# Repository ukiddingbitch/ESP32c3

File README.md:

# ESP32-C3

MIFA-F4 is a development board based on the **Espressif ESP32-C3FH4**, with 4 MB of flash, 2.4 GHz Wi-Fi, and Bluetooth LE. A meandered inverted-F antenna (MIFA) is etched into the PCB. Contacts on both sides of the board edge form the USB-C interface.

## Hardware

| Feature | Specification |
| --- | --- |
| Board size | 24.54 × 29.90 mm |
| PCB | 0.8 mm, two-layer FR-4 with an ENIG finish and castellated edge holes |
| Antenna | Meandered PCB antenna based on TI AN043 |
| Headers | Two rows of eight pins on a 2.54 mm pitch, spaced 20.32 mm apart center to center |
| Buttons | BOOT pulls GPIO9 low. RESET pulls EN low. |
| Assembly | 35 components per board |
| Panel | Six boards in a 3 × 2 layout, 95.62 × 80 mm, 210 component placements |

## Board

**Six-board assembly panel**

endfa

## Opening the design in KiCad

Download or clone the full repository to include the project libraries and 3D models. Open the [MIFA-F4 project](esp32c3mini-MIFA-F4/esp32c3mini.kicad_pro) in **KiCad 10**. Select the `.kicad_sch` file to view the schematic or the `.kicad_pcb` file to inspect the board layout. In the PCB Editor, press **Alt+3** to open the 3D Viewer.

## Fabrication and assembly

Choose the files for either a single board or a six-board panel. Use all three files from the same row.

| Format | PCB fabrication | Assembly parts list | Component positions and rotations |
| --- | --- | --- | --- |
| Single board | [Gerber ZIP](esp32c3mini-MIFA-F4/esp32c3mini-Gerber.zip) | [BOM](esp32c3mini-MIFA-F4/esp32c3mini-BOM.csv) | [CPL](esp32c3mini-MIFA-F4/esp32c3mini-CPL.csv) |
| Six-board panel | [Panel Gerber ZIP](esp32c3mini-MIFA-F4/panel/esp32c3mini-panel-Gerber.zip) | [Panel BOM](esp32c3mini-MIFA-F4/panel/esp32c3mini-panel-BOM.csv) | [Panel CPL](esp32c3mini-MIFA-F4/panel/esp32c3mini-panel-CPL.csv) |

For JLCPCB, upload the Gerber ZIP when ordering the PCB, then upload the matching BOM and CPL during assembly setup. Five assembled panels yield 30 individual boards.

## Prototype status and known limitations

**This board has not been physically tested.** The MIFA-F4 layout passed KiCad connectivity and schematic parity checks. Boot reliability, USB-C operation, power stability, and RF performance still require measurements on assembled hardware. Build and test a small prototype batch before ordering a production run.

### Before assembly

- Confirm the **0.8 mm PCB thickness** with the manufacturer. The board edge forms the USB-C mating surface, so thickness and routing tolerances affect the fit.
- Check the regulator orientation in the assembly preview. With the component side facing up and USB-C at the top, **U2 should have three leads toward USB-C and pin 1 at the upper right**. On the panel, the corresponding references are U102 through U602.

### First-prototype checks

| Area | What to verify |
| --- | --- |
| Power and boot | Check for a short between 3.3 V and GND before applying power. Use a current-limited supply for the first power-up, measure the 3.3 V rail, and check for voltage dips or resets during Wi-Fi transmission. Repeat cold starts to check boot reliability. |
| USB-C | Test plug fit, power delivery, USB detection, and firmware flashing in both plug orientations. Check that the connection stays stable during normal cable movement. Contact durability over repeated insertions is unverified. |
| BOOT and RESET | Confirm that holding BOOT while pressing and releasing RESET enters download mode, and that pressing RESET alone restarts the application. |
| Wi-Fi and antenna | Test a board **after separating it from the panel**. Compare signal strength and packet loss against a known-good ESP32-C3 board at the same distance and orientation on low, middle, and high Wi-Fi channels. Measure antenna return loss (S11) with a calibrated vector network analyzer to check impedance matching. |
| Board headers | Verify the 5 V, 3.3 V, and ground pins before connecting peripherals. Check the exposed GPIOs against the schematic and confirm the mechanical fit in the intended breadboard or carrier. |

The antenna layout follows TI AN043. Its range and susceptibility to interference from the nearby 40 MHz crystal are unverified on this PCB. See the [F4 validation notes](esp32c3mini-MIFA-F4/00-HOLD.txt) for layout dimensions and additional test details.

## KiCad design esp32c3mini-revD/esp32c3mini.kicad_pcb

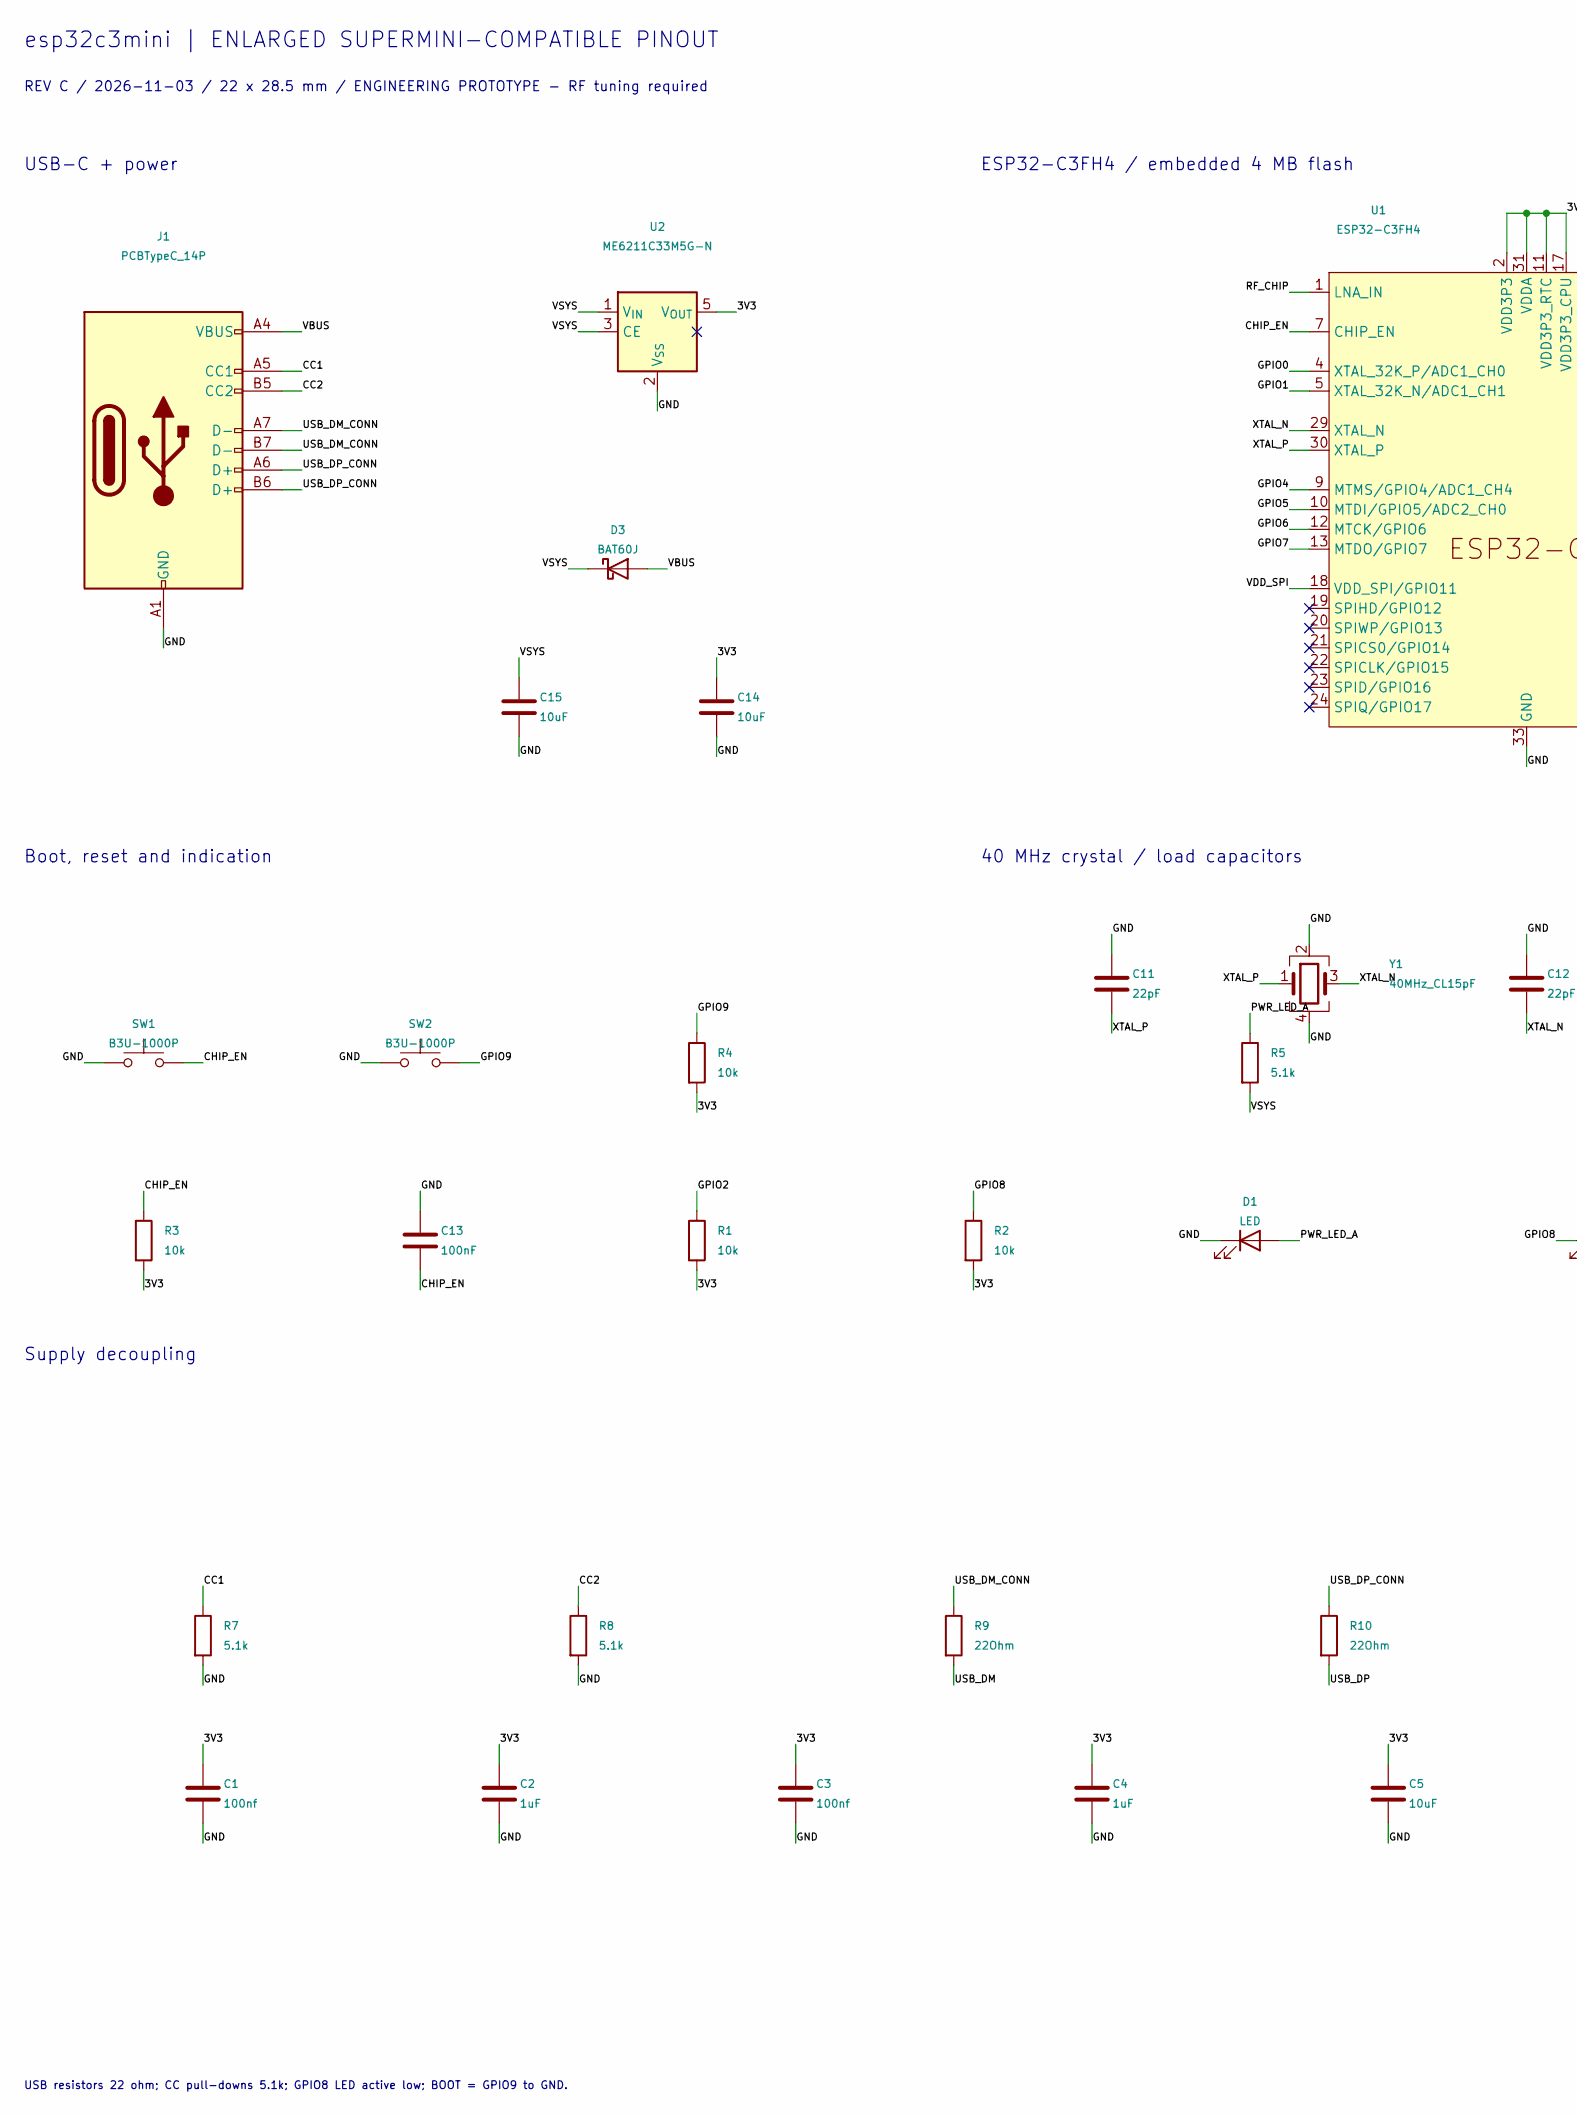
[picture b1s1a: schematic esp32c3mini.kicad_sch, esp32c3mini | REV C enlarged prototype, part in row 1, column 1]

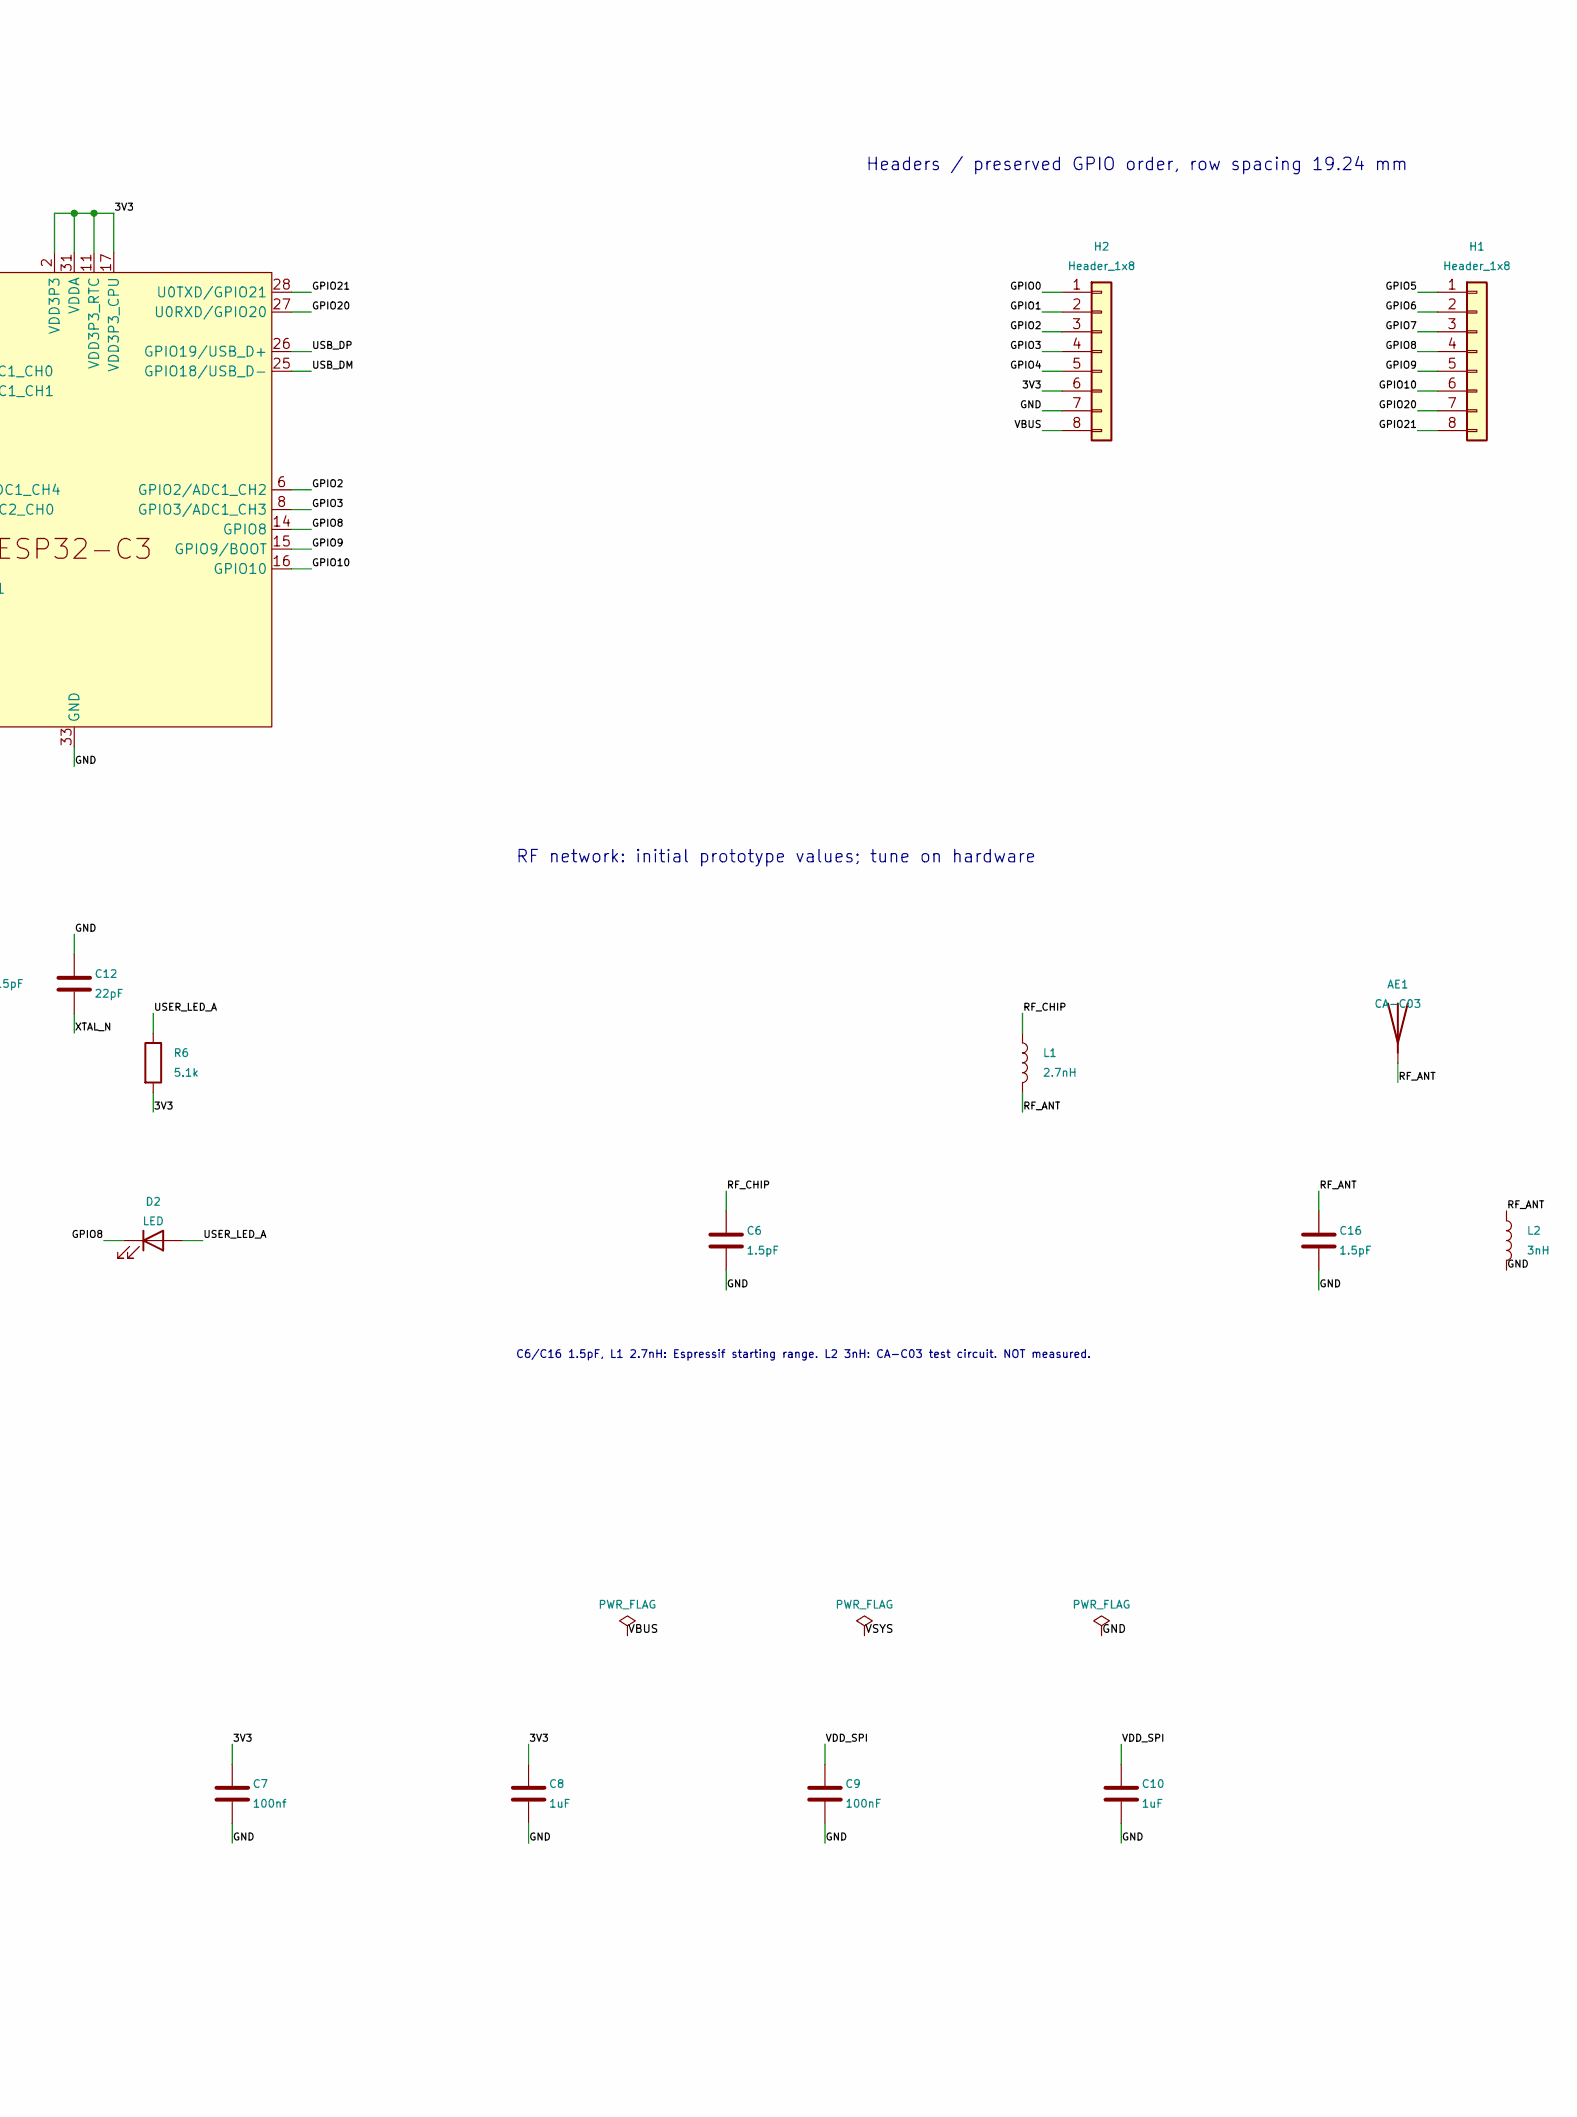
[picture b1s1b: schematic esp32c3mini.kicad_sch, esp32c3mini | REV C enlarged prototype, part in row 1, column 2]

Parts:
AE1: CA-C03; Antenna_CA_C03; MPN CA-C03; LCSC C9900104680
C1, C3, C7: 100nf; C_0201_0603Metric; MPN GRM033R61A104KE15D; LCSC C76934
C2, C4, C8, C10: 1uF; C_0201_0603Metric; MPN CL03A105KQ3CSNC; LCSC C318541
C5, C14, C15: 10uF; C_0402_1005Metric; MPN CL05A106MP5NUNC; LCSC C315248
C6, C16: 1.5pF; C_0201_0603Metric; MPN GRM0335C1H1R5BA01D; LCSC C161414
C9, C13: 100nF; C_0201_0603Metric; MPN GRM033R61A104KE15D; LCSC C76934
C11, C12: 22pF; C_0201_0603Metric; MPN GJM0335C1E220JB01D; LCSC C237453
D1: LED; LED_0603_1608Metric; MPN KT-0603R; LCSC C2286
D2: LED; LED_0603_1608Metric; MPN KT-0603B; LCSC C2288
D3: BAT60J; D_SOD-323; MPN BAT60JFILM; LCSC C133103
H1: Header_1x8; Header_Right
H2: Header_1x8; Header_Left
J1: PCBTypeC_14P; MPN PCB_EDGE_CONTACTS
L1: 2.7nH; L_0201_0603Metric; MPN LQP03TN2N7C02D; LCSC C185546
L2: 3nH; L_0201_0603Metric; MPN LQP03TN3N0C02D; LCSC C162614
R1, R2, R3, R4: 10k; R_0201_0603Metric; MPN 0201WMF1002TEE; LCSC C473048
R5, R6, R7, R8: 5.1k; R_0201_0603Metric; MPN 0201WMF5101TEE; LCSC C270344
R9, R10: 22Ohm; R_0201_0603Metric; MPN 0201WMF220JTEE; LCSC C270355
SW1, SW2: B3U-1000P; SW_SPST_B3U-1000P; MPN B3U-1000P; LCSC C231329
U1: ESP32-C3FH4; QFN-32-1EP_5x5mm_P0.5mm_EP3.45x3.45mm; MPN ESP32-C3FH4; LCSC C2858491
U2: ME6211C33M5G-N; SOT-23-5; MPN ME6211C33M5G-N; LCSC C82942
Y1: 40MHz_CL15pF; Crystal_SMD_3225-4Pin_3.2x2.5mm; MPN X322540MPB4SI; LCSC C9010

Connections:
/3V3: C1.1, C2.1, C3.1, C4.1, C5.1, C7.1, C8.1, C14.1, H2.6, R1.2, R2.2, R3.2, R4.2, R6.2, U1.2 (VDD3P3), U1.3 (VDD3P3), U1.11 (VDD3P3_RTC), U1.17 (VDD3P3_CPU), U1.31 (VDDA), U1.32 (VDDA), U2.5 (V_{OUT})
/CC1: J1.A5 (CC1), R7.1
/CC2: J1.B5 (CC2), R8.1
/CHIP_EN: C13.2, R3.1, SW1.2, U1.7 (CHIP_EN)
/GND: C1.2, C2.2, C3.2, C4.2, C5.2, C6.2, C7.2, C8.2, C9.2, C10.2, C11.1, C12.1, C13.1, C14.2, C15.2, C16.2, D1.1 (K), H2.7, J1.A1 (GND), J1.A12 (GND), J1.B1 (GND), J1.B12 (GND), L2.2, R7.2, R8.2, SW1.1, SW2.1, U1.33 (GND), U2.2 (V_{SS}), Y1.2, Y1.4
/GPIO0: H2.1, U1.4 (XTAL_32K_P/ADC1_CH0)
/GPIO1: H2.2, U1.5 (XTAL_32K_N/ADC1_CH1)
/GPIO2: H2.3, R1.1, U1.6 (GPIO2/ADC1_CH2)
/GPIO3: H2.4, U1.8 (GPIO3/ADC1_CH3)
/GPIO4: H2.5, U1.9 (MTMS/GPIO4/ADC1_CH4)
/GPIO5: H1.1, U1.10 (MTDI/GPIO5/ADC2_CH0)
/GPIO6: H1.2, U1.12 (MTCK/GPIO6)
/GPIO7: H1.3, U1.13 (MTDO/GPIO7)
/GPIO8: D2.1 (K), H1.4, R2.1, U1.14 (GPIO8)
/GPIO9: H1.5, R4.1, SW2.2, U1.15 (GPIO9/BOOT)
/GPIO10: H1.6, U1.16 (GPIO10)
/GPIO20: H1.7, U1.27 (U0RXD/GPIO20)
/GPIO21: H1.8, U1.28 (U0TXD/GPIO21)
/PWR_LED_A: D1.2 (A), R5.1
/RF_ANT: AE1.1, C16.1, L1.2, L2.1
/RF_CHIP: C6.1, L1.1, U1.1 (LNA_IN)
/USB_DM: R9.2, U1.25 (GPIO18/USB_D-)
/USB_DM_CONN: J1.A7 (D-), J1.B7 (D-), R9.1
/USB_DP: R10.2, U1.26 (GPIO19/USB_D+)
/USB_DP_CONN: J1.A6 (D+), J1.B6 (D+), R10.1
/USER_LED_A: D2.2 (A), R6.1
/VBUS: D3.2 (A), H2.8, J1.A4 (VBUS), J1.A9 (VBUS), J1.B4 (VBUS), J1.B9 (VBUS)
/VDD_SPI: C9.1, C10.1, U1.18 (VDD_SPI/GPIO11)
/VSYS: C15.1, D3.1 (K), R5.2, U2.1 (V_{IN}), U2.3 (CE)
/XTAL_N: C12.2, U1.29 (XTAL_N), Y1.3
/XTAL_P: C11.2, U1.30 (XTAL_P), Y1.1

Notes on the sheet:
esp32c3mini | ENLARGED SUPERMINI-COMPATIBLE PINOUT
REV C / 2026-11-03 / 22 x 28.5 mm / ENGINEERING PROTOTYPE - RF tuning required
USB-C + power
ESP32-C3FH4 / embedded 4 MB flash
Headers / preserved GPIO order, row spacing 19.24 mm
Boot, reset and indication
40 MHz crystal / load capacitors
RF network: initial prototype values; tune on hardware
Supply decoupling
C6/C16 1.5pF, L1 2.7nH: Espressif starting range. L2 3nH: CA-C03 test circuit. NOT measured.
USB resistors 22 ohm; CC pull-downs 5.1k; GPIO8 LED active low; BOOT = GPIO9 to GND.

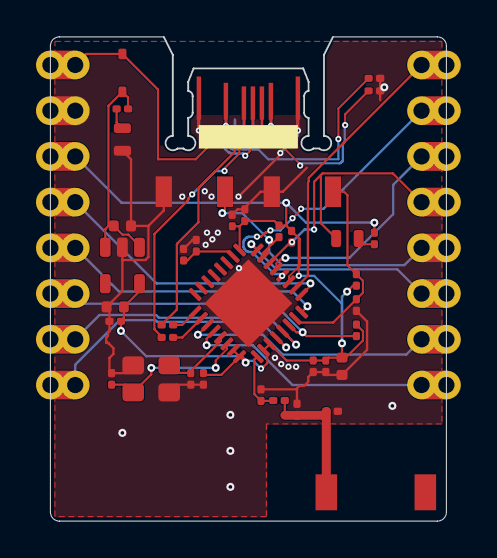
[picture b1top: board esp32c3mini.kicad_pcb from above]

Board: 2 copper layers, 22.0 x 26.9 mm, 40 parts (0 on the bottom side), 31 nets.

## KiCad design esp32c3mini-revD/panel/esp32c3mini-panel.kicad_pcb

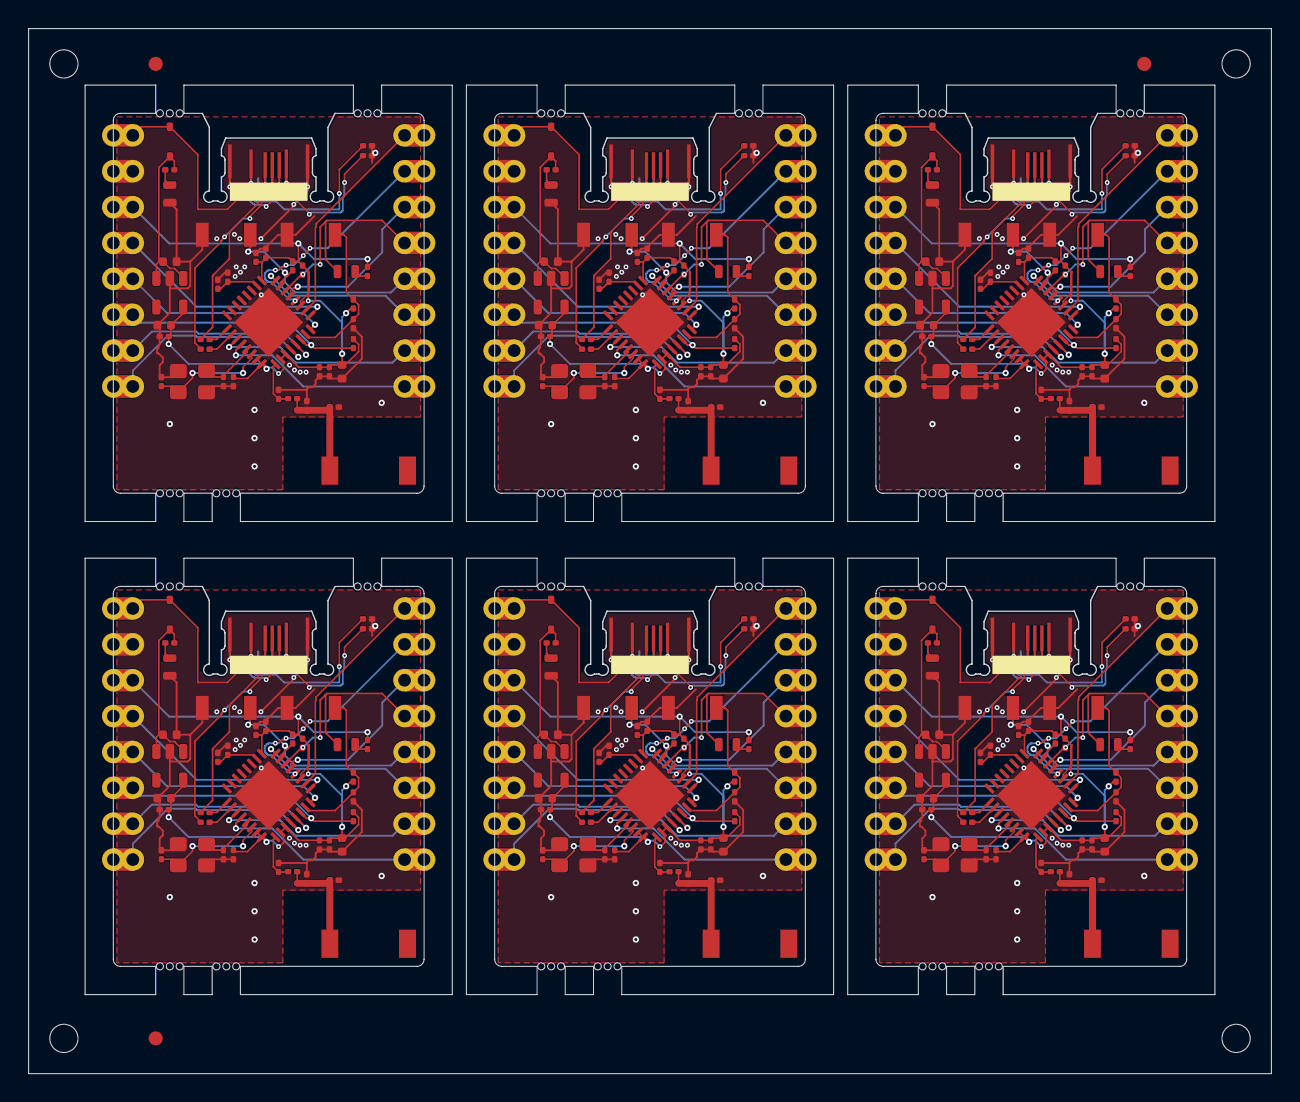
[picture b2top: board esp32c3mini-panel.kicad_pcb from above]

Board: 2 copper layers, 88.0 x 74.0 mm, 319 parts (0 on the bottom side), 186 nets.

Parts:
AE101, AE201, AE301, AE401, AE501, AE601: CA-C03; Antenna_CA_C03
C101, C103, C107, C201, C203, C207, C301, C303, C307, C401, C403, C407, C501, C503, C507, C601, C603, C607: 100nf; C_0201_0603Metric
C102, C104, C108, C110, C202, C204, C208, C210, C302, C304, C308, C310, C402, C404, C408, C410, C502, C504, C508, C510, C602, C604, C608, C610: 1uF; C_0201_0603Metric
C105, C114, C115, C205, C214, C215, C305, C314, C315, C405, C414, C415, C505, C514, C515, C605, C614, C615: 10uF; C_0402_1005Metric
C106, C116, C206, C216, C306, C316, C406, C416, C506, C516, C606, C616: 1.5pF; C_0201_0603Metric
C109, C113, C209, C213, C309, C313, C409, C413, C509, C513, C609, C613: 100nF; C_0201_0603Metric
C111, C112, C211, C212, C311, C312, C411, C412, C511, C512, C611, C612: 22pF; C_0201_0603Metric
D101, D102, D201, D202, D301, D302, D401, D402, D501, D502, D601, D602: LED; LED_0603_1608Metric
D103, D203, D303, D403, D503, D603: BAT60J; D_SOD-323
FID1, FID2, FID3: Fiducial
H101, H201, H301, H401, H501, H601: Header_1x8; Header_Right
H102, H202, H302, H402, H502, H602: Header_1x8; Header_Left
J101, J201, J301, J401, J501, J601: PCBTypeC_14P
L101, L201, L301, L401, L501, L601: 2.7nH; L_0201_0603Metric
L102, L202, L302, L402, L502, L602: 3nH; L_0201_0603Metric
MB1_4_106_0, MB1_4_106_1, MB1_4_106_2, MB1_4_132_0, MB1_4_132_1, MB1_4_132_2, MB1_8_132_0, MB1_8_132_1, MB1_8_132_2, MB1_18_106_0, MB1_18_106_1, MB1_18_106_2, MB2_4_106_0, MB2_4_106_1, MB2_4_106_2, MB2_4_132_0, MB2_4_132_1, MB2_4_132_2, MB2_8_132_0, MB2_8_132_1, MB2_8_132_2, MB2_18_106_0, MB2_18_106_1, MB2_18_106_2, MB3_4_106_0, MB3_4_106_1, MB3_4_106_2, MB3_4_132_0, MB3_4_132_1, MB3_4_132_2, MB3_8_132_0, MB3_8_132_1, MB3_8_132_2, MB3_18_106_0, MB3_18_106_1, MB3_18_106_2, MB4_4_139_0, MB4_4_139_1, MB4_4_139_2, MB4_4_166_0, MB4_4_166_1, MB4_4_166_2, MB4_8_166_0, MB4_8_166_1, MB4_8_166_2, MB4_18_139_0, MB4_18_139_1, MB4_18_139_2, MB5_4_139_0, MB5_4_139_1, MB5_4_139_2, MB5_4_166_0, MB5_4_166_1, MB5_4_166_2, MB5_8_166_0, MB5_8_166_1, MB5_8_166_2, MB5_18_139_0, MB5_18_139_1, MB5_18_139_2, MB6_4_139_0, MB6_4_139_1, MB6_4_139_2, MB6_4_166_0, MB6_4_166_1, MB6_4_166_2, MB6_8_166_0, MB6_8_166_1, MB6_8_166_2, MB6_18_139_0, MB6_18_139_1, MB6_18_139_2: NPTH; NPTH_0.5
R101, R102, R103, R104, R201, R202, R203, R204, R301, R302, R303, R304, R401, R402, R403, R404, R501, R502, R503, R504, R601, R602, R603, R604: 10k; R_0201_0603Metric
R105, R106, R107, R108, R205, R206, R207, R208, R305, R306, R307, R308, R405, R406, R407, R408, R505, R506, R507, R508, R605, R606, R607, R608: 5.1k; R_0201_0603Metric
R109, R110, R209, R210, R309, R310, R409, R410, R509, R510, R609, R610: 22Ohm; R_0201_0603Metric
SW101, SW102, SW201, SW202, SW301, SW302, SW401, SW402, SW501, SW502, SW601, SW602: B3U-1000P; SW_SPST_B3U-1000P
TH1, TH2, TH3, TH4: NPTH; NPTH_2
U101, U201, U301, U401, U501, U601: ESP32-C3FH4; QFN-32-1EP_5x5mm_P0.5mm_EP3.45x3.45mm
U102, U202, U302, U402, U502, U602: ME6211C33M5G-N; SOT-23-5
Y101, Y201, Y301, Y401, Y501, Y601: 40MHz_CL15pF; Crystal_SMD_3225-4Pin_3.2x2.5mm

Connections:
/B1/3V3: C101.1, C102.1, C103.1, C104.1, C105.1, C107.1, C108.1, C114.1, H102.6, R101.2, R102.2, R103.2, R104.2, R106.2, U101.2, U101.3, U101.11, U101.17, U101.31, U101.32, U102.5
/B1/CC1: J101.A5, R107.1
/B1/CC2: J101.B5, R108.1
/B1/CHIP_EN: C113.2, R103.1, SW101.2, U101.7
/B1/GND: C101.2, C102.2, C103.2, C104.2, C105.2, C106.2, C107.2, C108.2, C109.2, C110.2, C111.1, C112.1, C113.1, C114.2, C115.2, C116.2, D101.1, H102.7, J101.A1, J101.A12, J101.B1, J101.B12, L102.2, R107.2, R108.2, SW101.1, SW102.1, U101.33, U102.2, Y101.2, Y101.4
/B1/GPIO0: H102.1, U101.4
/B1/GPIO1: H102.2, U101.5
/B1/GPIO2: H102.3, R101.1, U101.6
/B1/GPIO3: H102.4, U101.8
/B1/GPIO4: H102.5, U101.9
/B1/GPIO5: H101.1, U101.10
/B1/GPIO6: H101.2, U101.12
/B1/GPIO7: H101.3, U101.13
/B1/GPIO8: D102.1, H101.4, R102.1, U101.14
/B1/GPIO9: H101.5, R104.1, SW102.2, U101.15
/B1/GPIO10: H101.6, U101.16
/B1/GPIO20: H101.7, U101.27
/B1/GPIO21: H101.8, U101.28
/B1/PWR_LED_A: D101.2, R105.1
/B1/RF_ANT: AE101.1, C116.1, L101.2, L102.1
/B1/RF_CHIP: C106.1, L101.1, U101.1
/B1/USB_DM: R109.2, U101.25
/B1/USB_DM_CONN: J101.A7, J101.B7, R109.1
/B1/USB_DP: R110.2, U101.26
/B1/USB_DP_CONN: J101.A6, J101.B6, R110.1
/B1/USER_LED_A: D102.2, R106.1
/B1/VBUS: D103.2, H102.8, J101.A4, J101.A9, J101.B4, J101.B9
/B1/VDD_SPI: C109.1, C110.1, U101.18
/B1/VSYS: C115.1, D103.1, R105.2, U102.1, U102.3
/B1/XTAL_N: C112.2, U101.29, Y101.3
/B1/XTAL_P: C111.2, U101.30, Y101.1
/B2/3V3: C201.1, C202.1, C203.1, C204.1, C205.1, C207.1, C208.1, C214.1, H202.6, R201.2, R202.2, R203.2, R204.2, R206.2, U201.2, U201.3, U201.11, U201.17, U201.31, U201.32, U202.5
/B2/CC1: J201.A5, R207.1
/B2/CC2: J201.B5, R208.1
/B2/CHIP_EN: C213.2, R203.1, SW201.2, U201.7
/B2/GND: C201.2, C202.2, C203.2, C204.2, C205.2, C206.2, C207.2, C208.2, C209.2, C210.2, C211.1, C212.1, C213.1, C214.2, C215.2, C216.2, D201.1, H202.7, J201.A1, J201.A12, J201.B1, J201.B12, L202.2, R207.2, R208.2, SW201.1, SW202.1, U201.33, U202.2, Y201.2, Y201.4
/B2/GPIO0: H202.1, U201.4
/B2/GPIO1: H202.2, U201.5
/B2/GPIO2: H202.3, R201.1, U201.6
/B2/GPIO3: H202.4, U201.8
/B2/GPIO4: H202.5, U201.9
/B2/GPIO5: H201.1, U201.10
/B2/GPIO6: H201.2, U201.12
/B2/GPIO7: H201.3, U201.13
/B2/GPIO8: D202.1, H201.4, R202.1, U201.14
/B2/GPIO9: H201.5, R204.1, SW202.2, U201.15
/B2/GPIO10: H201.6, U201.16
/B2/GPIO20: H201.7, U201.27
/B2/GPIO21: H201.8, U201.28
/B2/PWR_LED_A: D201.2, R205.1
/B2/RF_ANT: AE201.1, C216.1, L201.2, L202.1
/B2/RF_CHIP: C206.1, L201.1, U201.1
/B2/USB_DM: R209.2, U201.25
/B2/USB_DM_CONN: J201.A7, J201.B7, R209.1
/B2/USB_DP: R210.2, U201.26
/B2/USB_DP_CONN: J201.A6, J201.B6, R210.1
/B2/USER_LED_A: D202.2, R206.1
/B2/VBUS: D203.2, H202.8, J201.A4, J201.A9, J201.B4, J201.B9
/B2/VDD_SPI: C209.1, C210.1, U201.18
/B2/VSYS: C215.1, D203.1, R205.2, U202.1, U202.3
/B2/XTAL_N: C212.2, U201.29, Y201.3
/B2/XTAL_P: C211.2, U201.30, Y201.1
/B3/3V3: C301.1, C302.1, C303.1, C304.1, C305.1, C307.1, C308.1, C314.1, H302.6, R301.2, R302.2, R303.2, R304.2, R306.2, U301.2, U301.3, U301.11, U301.17, U301.31, U301.32, U302.5
/B3/CC1: J301.A5, R307.1
/B3/CC2: J301.B5, R308.1
/B3/CHIP_EN: C313.2, R303.1, SW301.2, U301.7
/B3/GND: C301.2, C302.2, C303.2, C304.2, C305.2, C306.2, C307.2, C308.2, C309.2, C310.2, C311.1, C312.1, C313.1, C314.2, C315.2, C316.2, D301.1, H302.7, J301.A1, J301.A12, J301.B1, J301.B12, L302.2, R307.2, R308.2, SW301.1, SW302.1, U301.33, U302.2, Y301.2, Y301.4
/B3/GPIO0: H302.1, U301.4
/B3/GPIO1: H302.2, U301.5
/B3/GPIO2: H302.3, R301.1, U301.6
/B3/GPIO3: H302.4, U301.8
/B3/GPIO4: H302.5, U301.9
/B3/GPIO5: H301.1, U301.10
/B3/GPIO6: H301.2, U301.12
/B3/GPIO7: H301.3, U301.13
/B3/GPIO8: D302.1, H301.4, R302.1, U301.14
/B3/GPIO9: H301.5, R304.1, SW302.2, U301.15
/B3/GPIO10: H301.6, U301.16
/B3/GPIO20: H301.7, U301.27
/B3/GPIO21: H301.8, U301.28
/B3/PWR_LED_A: D301.2, R305.1
/B3/RF_ANT: AE301.1, C316.1, L301.2, L302.1
/B3/RF_CHIP: C306.1, L301.1, U301.1
/B3/USB_DM: R309.2, U301.25
/B3/USB_DM_CONN: J301.A7, J301.B7, R309.1
/B3/USB_DP: R310.2, U301.26
/B3/USB_DP_CONN: J301.A6, J301.B6, R310.1
/B3/USER_LED_A: D302.2, R306.1
/B3/VBUS: D303.2, H302.8, J301.A4, J301.A9, J301.B4, J301.B9
/B3/VDD_SPI: C309.1, C310.1, U301.18
/B3/VSYS: C315.1, D303.1, R305.2, U302.1, U302.3
/B3/XTAL_N: C312.2, U301.29, Y301.3
/B3/XTAL_P: C311.2, U301.30, Y301.1
/B4/3V3: C401.1, C402.1, C403.1, C404.1, C405.1, C407.1, C408.1, C414.1, H402.6, R401.2, R402.2, R403.2, R404.2, R406.2, U401.2, U401.3, U401.11, U401.17, U401.31, U401.32, U402.5
/B4/CC1: J401.A5, R407.1
/B4/CC2: J401.B5, R408.1
/B4/CHIP_EN: C413.2, R403.1, SW401.2, U401.7
/B4/GND: C401.2, C402.2, C403.2, C404.2, C405.2, C406.2, C407.2, C408.2, C409.2, C410.2, C411.1, C412.1, C413.1, C414.2, C415.2, C416.2, D401.1, H402.7, J401.A1, J401.A12, J401.B1, J401.B12, L402.2, R407.2, R408.2, SW401.1, SW402.1, U401.33, U402.2, Y401.2, Y401.4
/B4/GPIO0: H402.1, U401.4
/B4/GPIO1: H402.2, U401.5
/B4/GPIO2: H402.3, R401.1, U401.6
/B4/GPIO3: H402.4, U401.8
/B4/GPIO4: H402.5, U401.9
/B4/GPIO5: H401.1, U401.10
/B4/GPIO6: H401.2, U401.12
/B4/GPIO7: H401.3, U401.13
/B4/GPIO8: D402.1, H401.4, R402.1, U401.14
/B4/GPIO9: H401.5, R404.1, SW402.2, U401.15
/B4/GPIO10: H401.6, U401.16
/B4/GPIO20: H401.7, U401.27
/B4/GPIO21: H401.8, U401.28
/B4/PWR_LED_A: D401.2, R405.1
/B4/RF_ANT: AE401.1, C416.1, L401.2, L402.1
/B4/RF_CHIP: C406.1, L401.1, U401.1
/B4/USB_DM: R409.2, U401.25
/B4/USB_DM_CONN: J401.A7, J401.B7, R409.1
/B4/USB_DP: R410.2, U401.26
/B4/USB_DP_CONN: J401.A6, J401.B6, R410.1
/B4/USER_LED_A: D402.2, R406.1
/B4/VBUS: D403.2, H402.8, J401.A4, J401.A9, J401.B4, J401.B9
/B4/VDD_SPI: C409.1, C410.1, U401.18
/B4/VSYS: C415.1, D403.1, R405.2, U402.1, U402.3
/B4/XTAL_N: C412.2, U401.29, Y401.3
/B4/XTAL_P: C411.2, U401.30, Y401.1
/B5/3V3: C501.1, C502.1, C503.1, C504.1, C505.1, C507.1, C508.1, C514.1, H502.6, R501.2, R502.2, R503.2, R504.2, R506.2, U501.2, U501.3, U501.11, U501.17, U501.31, U501.32, U502.5
/B5/CC1: J501.A5, R507.1
/B5/CC2: J501.B5, R508.1
/B5/CHIP_EN: C513.2, R503.1, SW501.2, U501.7
/B5/GND: C501.2, C502.2, C503.2, C504.2, C505.2, C506.2, C507.2, C508.2, C509.2, C510.2, C511.1, C512.1, C513.1, C514.2, C515.2, C516.2, D501.1, H502.7, J501.A1, J501.A12, J501.B1, J501.B12, L502.2, R507.2, R508.2, SW501.1, SW502.1, U501.33, U502.2, Y501.2, Y501.4
/B5/GPIO0: H502.1, U501.4
/B5/GPIO1: H502.2, U501.5
/B5/GPIO2: H502.3, R501.1, U501.6
/B5/GPIO3: H502.4, U501.8
/B5/GPIO4: H502.5, U501.9
/B5/GPIO5: H501.1, U501.10
/B5/GPIO6: H501.2, U501.12
/B5/GPIO7: H501.3, U501.13
/B5/GPIO8: D502.1, H501.4, R502.1, U501.14
/B5/GPIO9: H501.5, R504.1, SW502.2, U501.15
/B5/GPIO10: H501.6, U501.16
/B5/GPIO20: H501.7, U501.27
/B5/GPIO21: H501.8, U501.28
/B5/PWR_LED_A: D501.2, R505.1
/B5/RF_ANT: AE501.1, C516.1, L501.2, L502.1
/B5/RF_CHIP: C506.1, L501.1, U501.1
/B5/USB_DM: R509.2, U501.25
/B5/USB_DM_CONN: J501.A7, J501.B7, R509.1
/B5/USB_DP: R510.2, U501.26
/B5/USB_DP_CONN: J501.A6, J501.B6, R510.1
/B5/USER_LED_A: D502.2, R506.1
/B5/VBUS: D503.2, H502.8, J501.A4, J501.A9, J501.B4, J501.B9
/B5/VDD_SPI: C509.1, C510.1, U501.18
/B5/VSYS: C515.1, D503.1, R505.2, U502.1, U502.3
/B5/XTAL_N: C512.2, U501.29, Y501.3
/B5/XTAL_P: C511.2, U501.30, Y501.1
/B6/3V3: C601.1, C602.1, C603.1, C604.1, C605.1, C607.1, C608.1, C614.1, H602.6, R601.2, R602.2, R603.2, R604.2, R606.2, U601.2, U601.3, U601.11, U601.17, U601.31, U601.32, U602.5
/B6/CC1: J601.A5, R607.1
/B6/CC2: J601.B5, R608.1
/B6/CHIP_EN: C613.2, R603.1, SW601.2, U601.7
/B6/GND: C601.2, C602.2, C603.2, C604.2, C605.2, C606.2, C607.2, C608.2, C609.2, C610.2, C611.1, C612.1, C613.1, C614.2, C615.2, C616.2, D601.1, H602.7, J601.A1, J601.A12, J601.B1, J601.B12, L602.2, R607.2, R608.2, SW601.1, SW602.1, U601.33, U602.2, Y601.2, Y601.4
/B6/GPIO0: H602.1, U601.4
/B6/GPIO1: H602.2, U601.5
/B6/GPIO2: H602.3, R601.1, U601.6
/B6/GPIO3: H602.4, U601.8
/B6/GPIO4: H602.5, U601.9
/B6/GPIO5: H601.1, U601.10
/B6/GPIO6: H601.2, U601.12
/B6/GPIO7: H601.3, U601.13
/B6/GPIO8: D602.1, H601.4, R602.1, U601.14
/B6/GPIO9: H601.5, R604.1, SW602.2, U601.15
/B6/GPIO10: H601.6, U601.16
/B6/GPIO20: H601.7, U601.27
/B6/GPIO21: H601.8, U601.28
/B6/PWR_LED_A: D601.2, R605.1
/B6/RF_ANT: AE601.1, C616.1, L601.2, L602.1
/B6/RF_CHIP: C606.1, L601.1, U601.1
/B6/USB_DM: R609.2, U601.25
/B6/USB_DM_CONN: J601.A7, J601.B7, R609.1
/B6/USB_DP: R610.2, U601.26
/B6/USB_DP_CONN: J601.A6, J601.B6, R610.1
/B6/USER_LED_A: D602.2, R606.1
/B6/VBUS: D603.2, H602.8, J601.A4, J601.A9, J601.B4, J601.B9
/B6/VDD_SPI: C609.1, C610.1, U601.18
/B6/VSYS: C615.1, D603.1, R605.2, U602.1, U602.3
/B6/XTAL_N: C612.2, U601.29, Y601.3
/B6/XTAL_P: C611.2, U601.30, Y601.1
